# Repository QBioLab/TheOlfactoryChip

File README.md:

# TheOlfactoryChip
The code and draw of design

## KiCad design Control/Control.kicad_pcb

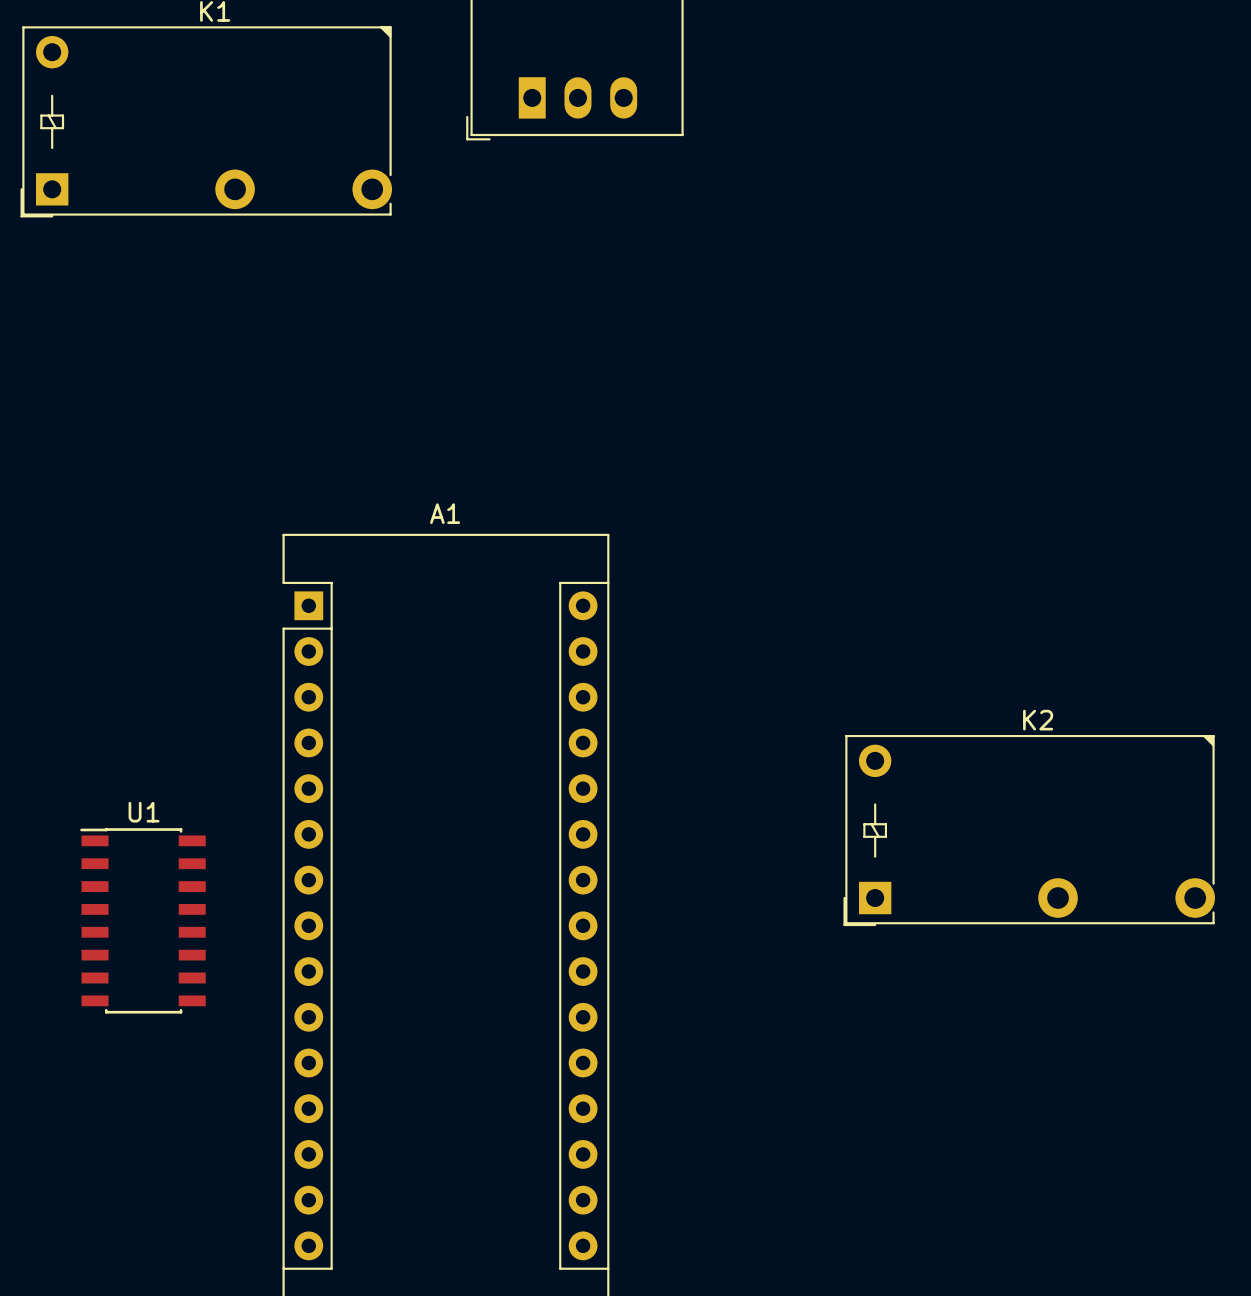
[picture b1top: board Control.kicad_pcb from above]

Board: 2 copper layers, 5 parts (0 on the bottom side), 9 nets, no tracks yet.

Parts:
A1: Arduino_Nano_v2.x; Arduino_Nano
K1, K2: FINDER-32.21-x300; Relay_SPST_Finder_32.21-x300
U1: DG308AxY; SOIC-16_3.9x9.9mm_P1.27mm
U2: R-781.5-0.5; Converter_DCDC_RECOM_R-78E-0.5_THT

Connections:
+12V: K1.14, K2.14, U2.1
Earth: A1.29, K1.A2, K2.A2, U2.2
unnamed: A1.5, K1.A1
unnamed: A1.6, K2.A1
unnamed: A1.7, U1.3
unnamed: A1.8, U1.2
unnamed: A1.9, U1.7
unnamed: A1.10, U1.6
unnamed: A1.30, U2.3

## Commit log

2019-01-13 upload
2019-01-30 using rtos instead of loop()
2019-04-22 try to add PID control
2019-08-24 update rtos_ctrl
2019-12-05 update SyringeHolder
2019-12-06 update syringholder
